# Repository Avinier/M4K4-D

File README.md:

# Makad / M4K4-D

> **Current project overview**: last reconciled **12 November 2026**
>
> Foundation approved: **14 August 2026** · V1 deadline: **5 December 2026**

**Makad**, technical designation **M4K4-D** and commonly shortened to **M4**, is a personal droid. M4 is intended to occupy the kind of companion role R2-D2 occupied for Luke Skywalker: recognizable, attentive, expressive, and full of character.

The central V1 priority is simple:

> **M4 should feel alive.**

Makad's defining advantage is expressiveness. That expression comes from what M4 understands, sees, and hears, and from how convincingly its display, status light, astromech audio, head, wheeled base, and timing communicate one intent.

## Authority

- [`project/00-foundation`](project/00-foundation/) is the product-intent authority.
- [`project/03-build`](project/03-build/README.md) governs every engineering decision, part selection, BOM change and CAD edit from 2026-09-28. Its ledger is [`decisions.md`](project/03-build/decisions.md) and its parts register is [`BOM.csv`](project/03-build/BOM.csv).
- [`project/01-system`](project/01-system/) and [`project/02-prototypes`](project/02-prototypes/) are read-only engineering reference. Where they disagree with `03-build`, `03-build` wins.

[`MEMORY.md`](MEMORY.md) is a short chronological log of the project's turning points.

## Current design

M4 is a battery-powered floor droid with a three-axis head, an animated face, a camera-side status light, body-mounted hearing and speech, and a two-wheel base. The head carries the display, camera, status light and C2 motion controller. The body carries the yaw stage, four I²S microphones, the speaker, main compute and the bought power modules; the chassis carries the battery, drive and floor sensors. Floor mode is primary; tabletop mode inhibits locomotion by default.

Drive geometry is Ø84 mm wheels on a ~170 mm track with a front ball caster and a mandatory rear anti-tip keel ([dimensional baseline](project/01-system/dimensional-baseline.md) v1.15). The whole robot is modelled in [`project/03-build/final/v1`](project/03-build/final/v1/README.md); subsystem CAD lives in [01-chassis](project/03-build/01-chassis/), [02-body](project/03-build/02-body/) and [03-head](project/03-build/03-head/).

### Selected components

States follow the [BOM](project/03-build/BOM.csv): selected parts are settled but not yet measured or bench-proven.

| Item | Selection | Record |
|---|---|---|
| Face display | Waveshare ESP32-S3-LCD-4.3, **no-touch, SKU 30493**: 800×480 IPS with on-board ESP32-S3/LVGL renderer | [display study](project/01-system/display-candidate-study.md) |
| Head camera | Raspberry Pi Camera Module 3 **Wide**, **SC0874**; ribbon crosses pitch and roll in a free loop behind the head | [D-105](project/03-build/decisions.md#d-105) |
| Main compute (C0) | **Raspberry Pi 5, 2 GB** with the official Active Cooler, on PCB-09 (2 × RS-422 link adapter) | [D-048](project/03-build/decisions.md#d-048), [04-pcbs](project/03-build/04-pcbs/README.md) |
| Head motion controller (C2) | Waveshare **ESP32-S3-Zero** on the custom PCB-12 carrier | [D-102](project/03-build/decisions.md#d-102) |
| Base controller (C3) | Espressif **ESP32-S3-DevKitC-1 v1.1** on the custom PCB-10 carrier | [04-pcbs](project/03-build/04-pcbs/README.md) |
| Head actuators | Yaw: **Waveshare ST3215-HS** at 11.1 V. Pitch and roll: **Feetech STS3045M** at 6.3 V. Candidates until bench tests B1–B6 | [D-046](project/03-build/decisions.md#d-046)–[D-049](project/03-build/decisions.md#d-049) |
| Drive | **ThinkRobotics MOT3001-6V230RPM** encoder gearmotors (received), two DRV8833 carriers, printed PETG/TPU wheels, Pololu #2691 ball caster | [D-003](project/03-build/decisions.md#d-003) |
| Battery | **2S1P Samsung INR18650-25R** (7.2 V, 18 Wh) with a bought TIFPS0629 protection board and copper ballast; charged off-board (ISDT PD60) | [D-093](project/03-build/decisions.md#d-093) |
| Power | Pololu #2813 pushbutton switch, two S18V20ALV servo rails, two S13V30F5 5 V rails, INA226 monitor | [D-094](project/03-build/decisions.md#d-094), [module selection](project/03-build/module-selection.md) |
| Audio and IMU | Visaton K 50 WP speaker, MAX98357A amp, 4 × INMP441 mics, Adafruit LSM6DSOX base IMU | [D-094](project/03-build/decisions.md#d-094) |
| Control split | C0 owns semantic behaviour; D1 renders eyes; C2 owns head trajectory and local safety; C3 owns base loops and local hazards. Links are differential UART; C2 relays face/light state locally | [control topology](project/01-system/control-topology-options.md) |

## Current build state

The design is ahead of the physical robot. The whole-robot CAD is integrated and checked; first parts have arrived; nothing is printed, wired or running.

| Area | State (2026-11-12) |
|---|---|
| CAD | Chassis, body and head v1 are integrated in `final/v1` with targeted checks. Tipping margin a_tip 1.670 neutral / 1.646 worst pose against 1.582 ([D-095](project/03-build/decisions.md#d-095)); camera-loop ballast keeps the worst-yaw margin above 1.5% ([D-105](project/03-build/decisions.md#d-105)). Not yet a fabrication release for body and head. |
| Electrical | D-093 replaced the custom power boards with bought modules. The [harness](project/03-build/05-harness/README.md) topology is drawn but on **electrical HOLD** ([D-096](project/03-build/decisions.md#d-096)). Custom boards: PCB-09 rev B routed; PCB-10/11/15 rev A; PCB-08/12/14/16 rev A drafts, not ordered. |
| Procurement | Modules and small parts ordered 2026-11-08; deliveries logged in [BOM-deliveries.md](project/03-build/BOM-deliveries.md). Open actions in [TODO.md](project/03-build/TODO.md). |
| Printing | Chassis print package exported to [04-print](project/04-print/README.md); body and head prints not started. |
| Software / firmware | [Firmware requirements](project/03-build/04-software/firmware-requirements.md) recorded; timebase, link contract and behaviour are specified more than implemented. |
| Physical tests | None run. Bench register N1–N12 and actuator tests B1–B6 are open. |

`visuals/` are provisional references; several show superseded details (mouths, ear microphones, yoke-mounted ears).

## Immediate next work

- **Receive and measure** the ordered parts; record them in the BOM and correct dependent CAD.
- **Run the bench tests**: power switch, servo and 5 V rails (N1–N12), Feetech actuators (B1–B6), pack protection acceptance.
- **Clear the harness HOLD** from measured peaks, then build and test the harness.
- **Finish the custom boards** (PCB-08, 12, 14, 16) and order all of them together.
- **Print and assemble the chassis**, then body and head, through [04-print](project/04-print/README.md).
- **Implement firmware and software** on the same timeline: C2/C3, C0 behaviour and perception, the serial link and face rendering.

## Documents

### Product intent: authoritative

- [Vision](project/00-foundation/vision.md)
- [V1 scope](project/00-foundation/v1-scope.md)
- [Constraints](project/00-foundation/constraints.md)
- [Success criteria](project/00-foundation/success-criteria.md)
- [Core interaction scenarios](project/00-foundation/core-interaction-scenarios.md)

### Build: governing

- [03-build overview](project/03-build/README.md): status, file map and build rules
- [Decisions ledger](project/03-build/decisions.md), [BOM](project/03-build/BOM.csv), [simplification plan](project/03-build/simplification-plan.md)
- [Whole robot (final v1)](project/03-build/final/v1/README.md) and its [print guide](project/03-build/final/v1/printguide.md)
- [Custom PCBs](project/03-build/04-pcbs/README.md), [harness](project/03-build/05-harness/README.md)
- [Printing](project/04-print/README.md)

### Engineering reference (read-only)

- [Dimensional and packaging baseline](project/01-system/dimensional-baseline.md)
- Ledgers: [mass/envelope](project/01-system/mass-envelope-ledger.md), [power/energy/thermal](project/01-system/power-energy-ledger.md), [candidate sourcing](project/01-system/candidate-sourcing-matrix.md)
- Studies: [control topology](project/01-system/control-topology-options.md), [display](project/01-system/display-candidate-study.md), [camera](project/01-system/camera-candidate-study.md), [head harness](project/01-system/head-harness-routing-study.md), [timebase](project/01-system/timebase.md)
- [System design brief](project/01-system/system-design-brief.md), [risk-prototype plan](project/01-system/risk-prototype-plan.md), [workbench](project/01-system/workbench.md), [run-record convention](project/01-system/run-record-convention.md)
- Risk prototypes: [head](project/02-prototypes/RP-01-head/), [electrical](project/02-prototypes/RP-02-electrical/README.md), [locomotion](project/02-prototypes/RP-03-locomotion/README.md), [coordination](project/02-prototypes/RP-04-coordination/README.md), [interaction](project/02-prototypes/RP-05-interaction/README.md), [CAD layouts](project/02-prototypes/RP-06-cad/README.md), [following](project/02-prototypes/RP-07-following/README.md)
- Earlier memory logs: [`archive/`](archive/)

## Repository

```
project/00-foundation/   product intent and constraints      authoritative
project/01-system/       system studies and ledgers          reference
project/02-prototypes/   risk prototypes and early CAD       reference
project/03-build/        decisions, BOM, CAD, PCBs, harness  governs
project/04-print/        print lab, workflow, STL exports
visuals/                 provisional renders
archive/                 earlier memory logs
MEMORY.md                chronological log of turning points
README.md                this orientation
```

## Identity and design direction

M4 is a droid, not a desktop assistant, smart speaker, or generic social robot. The approved direction is:

- strongly inspired by Star Wars droids;
- cyberpunk, rugged, scrappy, and characterful;
- mechanical rather than glossy or appliance-like;
- modular and screw-together, with visible fasteners, panels, seams, and service access as part of the personality;
- eyes only on the face, no mouth;
- approachable without optimizing for minimum size;
- open to substantial redesign from the current renders.

## V1 Core

V1 is not complete unless the following outcomes work together as one droid. Exact wording lives in [`v1-scope.md`](project/00-foundation/v1-scope.md) (SCOPE-01…21).

**Expression and character** — animated face on the onboard display; powered roll, pitch and yaw head motion; at least one controllable LED beside the camera; a builder-authored non-English astromech language; idle aliveness without manual control; display, LED, audio, head, base and timing express one intent; at least one bounded excited spin.

**Understanding and perception** — natural spoken interaction within the approved scenarios; invocation forms **"M4," "M4K4," and "Makad"**; visual acquisition of a nearby person or face; tracking maintained or reacquired through later-defined test cases.

**Mobility and following** — battery-powered wheeled floor droid; "come here" finds, approaches and stops at a bounded distance; "follow me" tracks the selected person through an approved indoor route; obstacles, stopping, target loss and unsafe conditions are handled without continuing blindly.

**Utility and entertainment** — display the time; create and signal timers and alarms; start Spotify playback through an approved integration; eyes "vibe" to music.

**Operation and construction** — untethered on onboard battery for at least 20 minutes; floor mode primary; tabletop mode inhibits locomotion by default and protects edges; accessible stop or cutoff with bounded failure; assembled, started, demonstrated, inspected and serviced from documentation.

**Candidate:** spatial/directional hearing, included only if it materially improves an approved interaction. Everything else is uncommitted; there is no permanent "never" list.

## Approved Core scenarios

Source: [`core-interaction-scenarios.md`](project/00-foundation/core-interaction-scenarios.md).

**1. Wake, socialize, assist.** M4 idles head-down. A person calls its name. M4 wakes as one coordinated performance: three-axis head rise, eyes, camera-side LED, astromech acknowledgement, face acquisition and gaze. A greeting produces an in-character response. The person can request the time, a timer, an alarm, or Spotify playback; M4 confirms visibly, performs it, and vibes during music.

**2. Come here and follow me.** On an approved floor, the person invokes M4 and says "come here." M4 acknowledges, searches, acquires, turns, approaches safely and stops approximately 0.6–0.9 m away. "Follow me" makes M4 follow through an approved route of up to about 3 m at no more than about 0.5 m/s while handling obstacles and target loss. When continuing is unsafe, M4 stops and says so. M4 performs an excited spin and settles.

## Success definition

V1 succeeds when M4 delivers these interactions as a convincing, repeatable droid encounter on battery power, not as a sequence of manually rescued subsystem demos. The validation categories and open thresholds are in [`success-criteria.md`](project/00-foundation/success-criteria.md) (SC-01…25).

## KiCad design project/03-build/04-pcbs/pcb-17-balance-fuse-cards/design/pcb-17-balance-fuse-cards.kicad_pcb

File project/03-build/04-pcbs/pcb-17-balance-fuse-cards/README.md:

# PCB-17 — Balance-tap fuse cards

Two small passive cards that put a 1 A very-fast fuse in each of the pack's three balance taps (B−, BM, B+) right at the PCB-01 BMS pads. These taps feed the rear balance port ahead of PCB-01 and the 15 A main fuse, so the cards are their only short-circuit protection ([D-111](../../decisions.md#d-111), [D-115](../../decisions.md#d-115), [D-116](../../decisions.md#d-116), [D-117](../../decisions.md#d-117)).

| | |
|---|---|
| Register | [04-pcbs board register](../README.md#board-register) |
| Project BOM | CH-103 in [BOM.csv](../../BOM.csv) |
| Location | Chassis tub, lying component side up on the PCB-01 (HW-391) BMS: card A at its +Y (BM/P) end, card B at its −Y (0V/8.4V) end, each under a 0.8 mm relief in the CH-106 plate |
| Final CAD | `BALANCE_FUSE` and `BMS_PADS` in [makad-v1.step.py](../../final/v1/cad/makad-v1.step.py); check `check_ch103_protection.py` |

## Stages

| Stage | Status | Revision / evidence | Date |
|---|---|---|---|
| 1. Design | **Rev A complete**; [fab/revA](fab/revA/README.md) written (do not order before the gates) | [design/](design/): Nightly ERC 0/0, netlist audit 13/13, parity DRC 0/0/0; [STEP](cad/pcb-17-balance-fuse-cards-revA.step) | 2026-11-18 |
| 2. Procure | Panelise with PCB-11 and PCB-15 (same 0.8 mm stackup) in the D-064 batch | — | — |
| 3. Integrate | Droid CAD envelopes match the KiCad outlines (card A 6 × 9, card B 9.5 × 10, 2.0 mm with fuse and potting); `check_ch103_protection` 12/12. Board STEP not yet swapped in by `pcb_integration.py` | Physical acceptance open | 2026-11-18 |

## Circuit

| Card | Fuse | Cell-side pad | Protected pad | Silk |
|---|---|---|---|---|
| A (6 × 9 mm) | F1, BM | J1 `BM_CELL` (from the HW-391 4.2V pad) | J2 `BM_FUSED` | `BM`; back `17A` |
| B (9.5 × 10 mm) | F2, B− | J3 `BMINUS_CELL` (0V pad) | J4 `BMINUS_FUSED` | `B-`; back `17B` |
| B | F3, B+ | J5 `BPLUS_CELL` (8.4V pad) | J6 `BPLUS_FUSED` | `B+` |

Fuses: Littelfuse 0466001.NRHF, 1206, 1 A, 63 VDC, 50 A interrupt, ~0.075 Ω cold. Each fuse's pin 1 faces its card's BMS pad end. Wire pads are 2.5 × 1.5 mm bare copper for AWG24 laid flat along X. Tracks are 0.8 mm, one straight column per tap. B− and B+ copper is 1.5 mm apart.

## Coordinates

KiCad (x, y down) to droid CAD: card A X = x − 59.0, Y = 124.0 − y; card B X = x − 70.7, Y = 86.0 − y. Board Z 0 is the card's underside on the BMS (droid Z 54.2). Fab origin (100, 110), the bottom-left of the two-card group.

## Open

- **Received HW-391:** confirm the pad corners (the `BMS_PADS` values are estimates from the listing photos) and the full board height. If board + card exceeds the pack-to-plate gap at either end, deepen that CH-106 relief, keeping at least a 1.5 mm roof, and re-run `check_ch103_protection.py`.
- **Potting:** thin silicone or epoxy, ≤ 0.6 mm over the fuse. The fuse ratings assume an uncoated part, so N5 is run with the cards potted ([D-116](../../decisions.md#d-116)).
- **N5:** the PD60 open-tap, adjacent-short and main-lead-off cases, plus 0.5 A fuse heating, per D-116. W02P stays unbuilt until N5 passes.

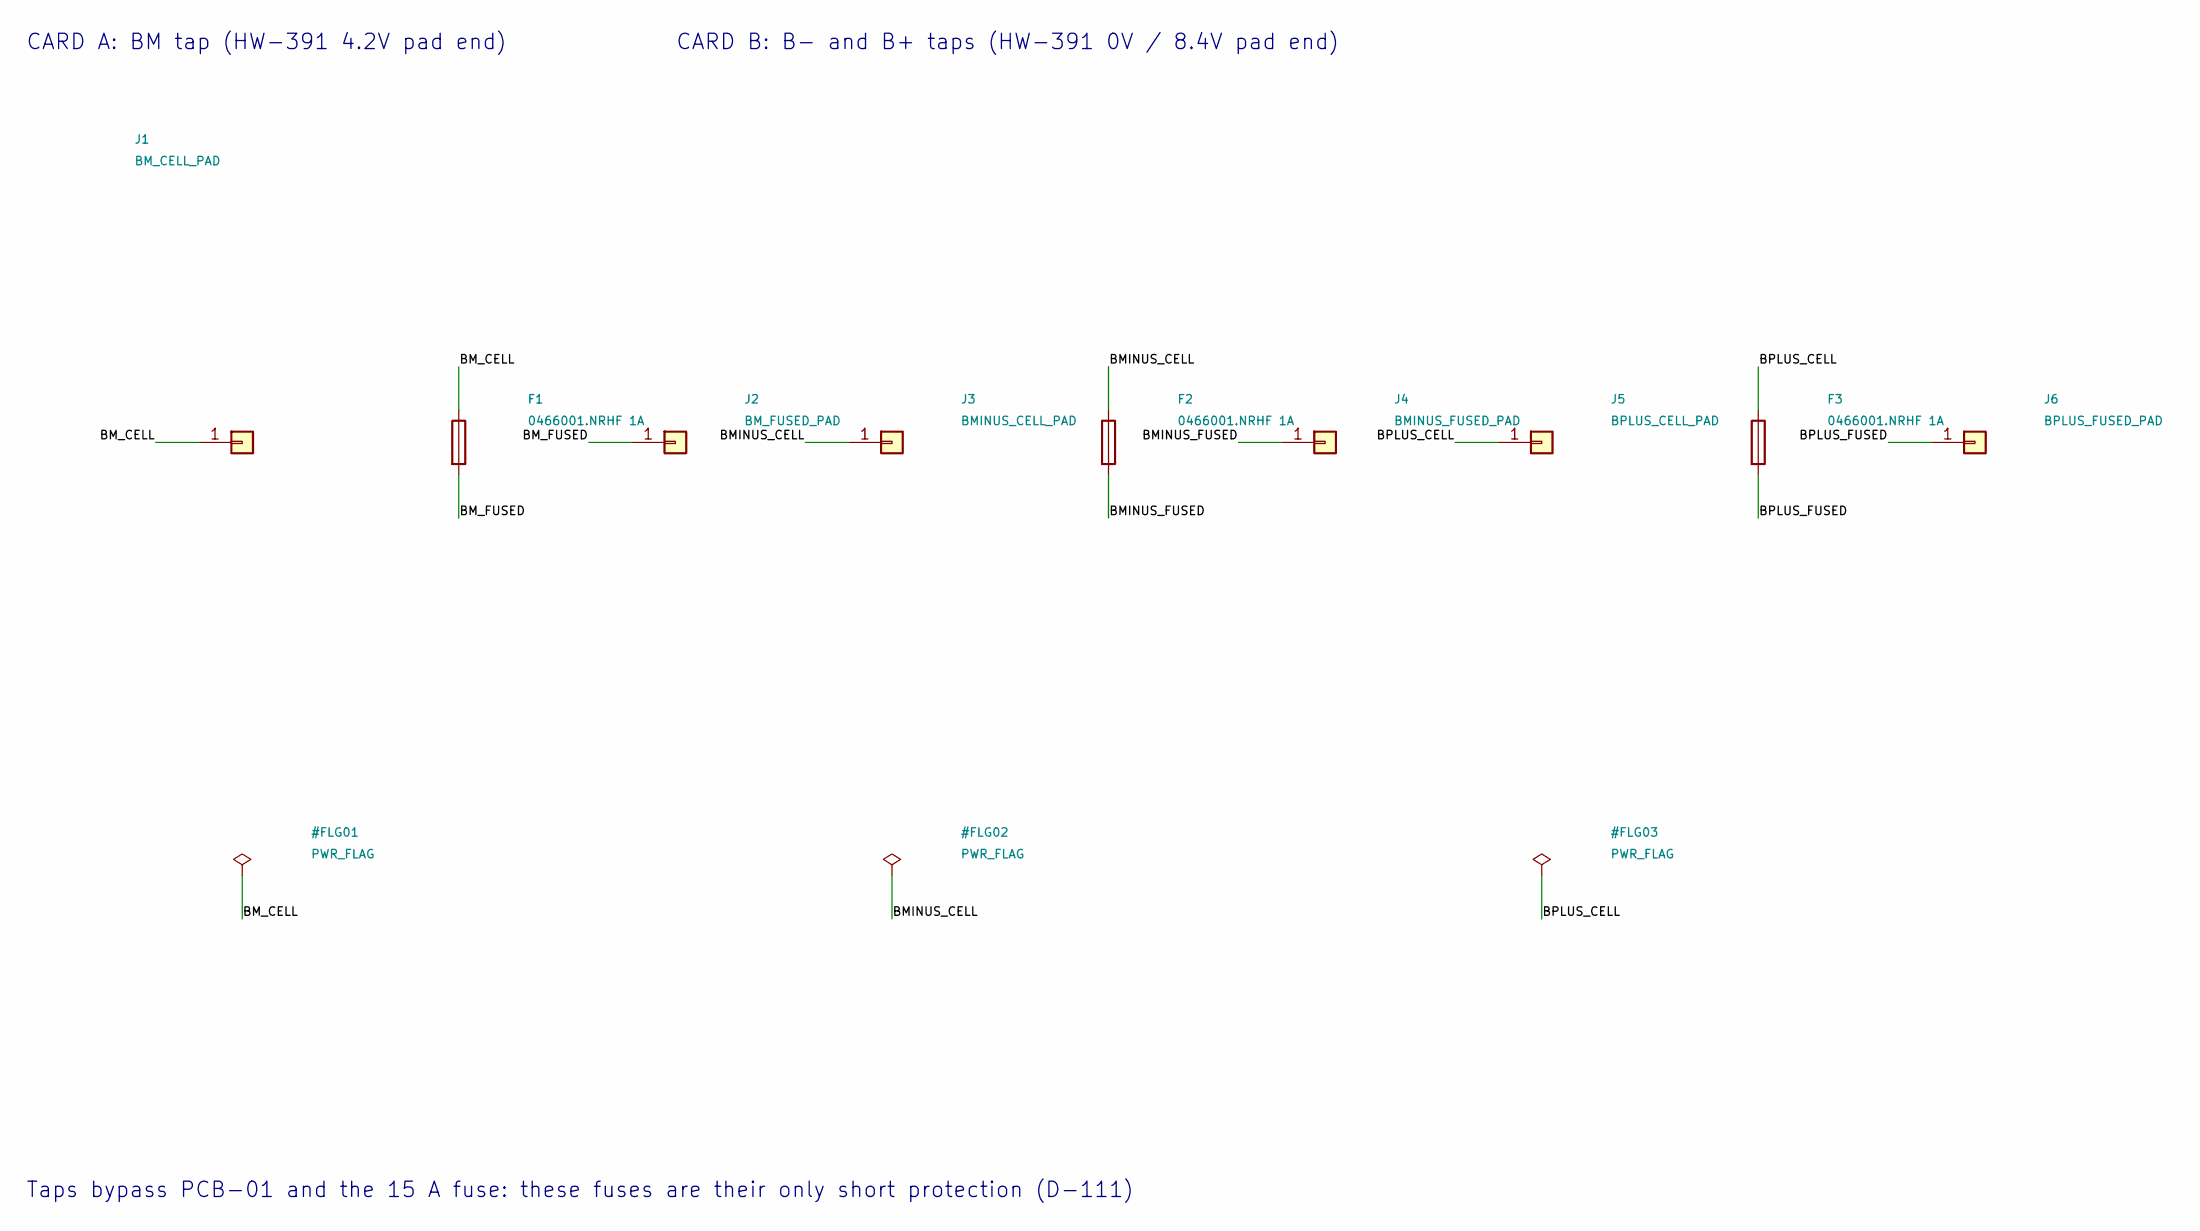
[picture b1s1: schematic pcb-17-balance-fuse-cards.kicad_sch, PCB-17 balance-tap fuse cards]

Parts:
F1, F2, F3: 0466001.NRHF 1A; Fuse_1206_3216Metric
J1: BM_CELL_PAD; WirePad_1x01_2.5x1.5mm
J2: BM_FUSED_PAD; WirePad_1x01_2.5x1.5mm
J3: BMINUS_CELL_PAD; WirePad_1x01_2.5x1.5mm
J4: BMINUS_FUSED_PAD; WirePad_1x01_2.5x1.5mm
J5: BPLUS_CELL_PAD; WirePad_1x01_2.5x1.5mm
J6: BPLUS_FUSED_PAD; WirePad_1x01_2.5x1.5mm

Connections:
/BMINUS_CELL: F2.1, J3.1 (Pin_1_1)
/BMINUS_FUSED: F2.2, J4.1 (Pin_1_1)
/BM_CELL: F1.1, J1.1 (Pin_1_1)
/BM_FUSED: F1.2, J2.1 (Pin_1_1)
/BPLUS_CELL: F3.1, J5.1 (Pin_1_1)
/BPLUS_FUSED: F3.2, J6.1 (Pin_1_1)

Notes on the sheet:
CARD A: BM tap (HW-391 4.2V pad end)
CARD B: B- and B+ taps (HW-391 0V / 8.4V pad end)
Taps bypass PCB-01 and the 15 A fuse: these fuses are their only short protection (D-111)

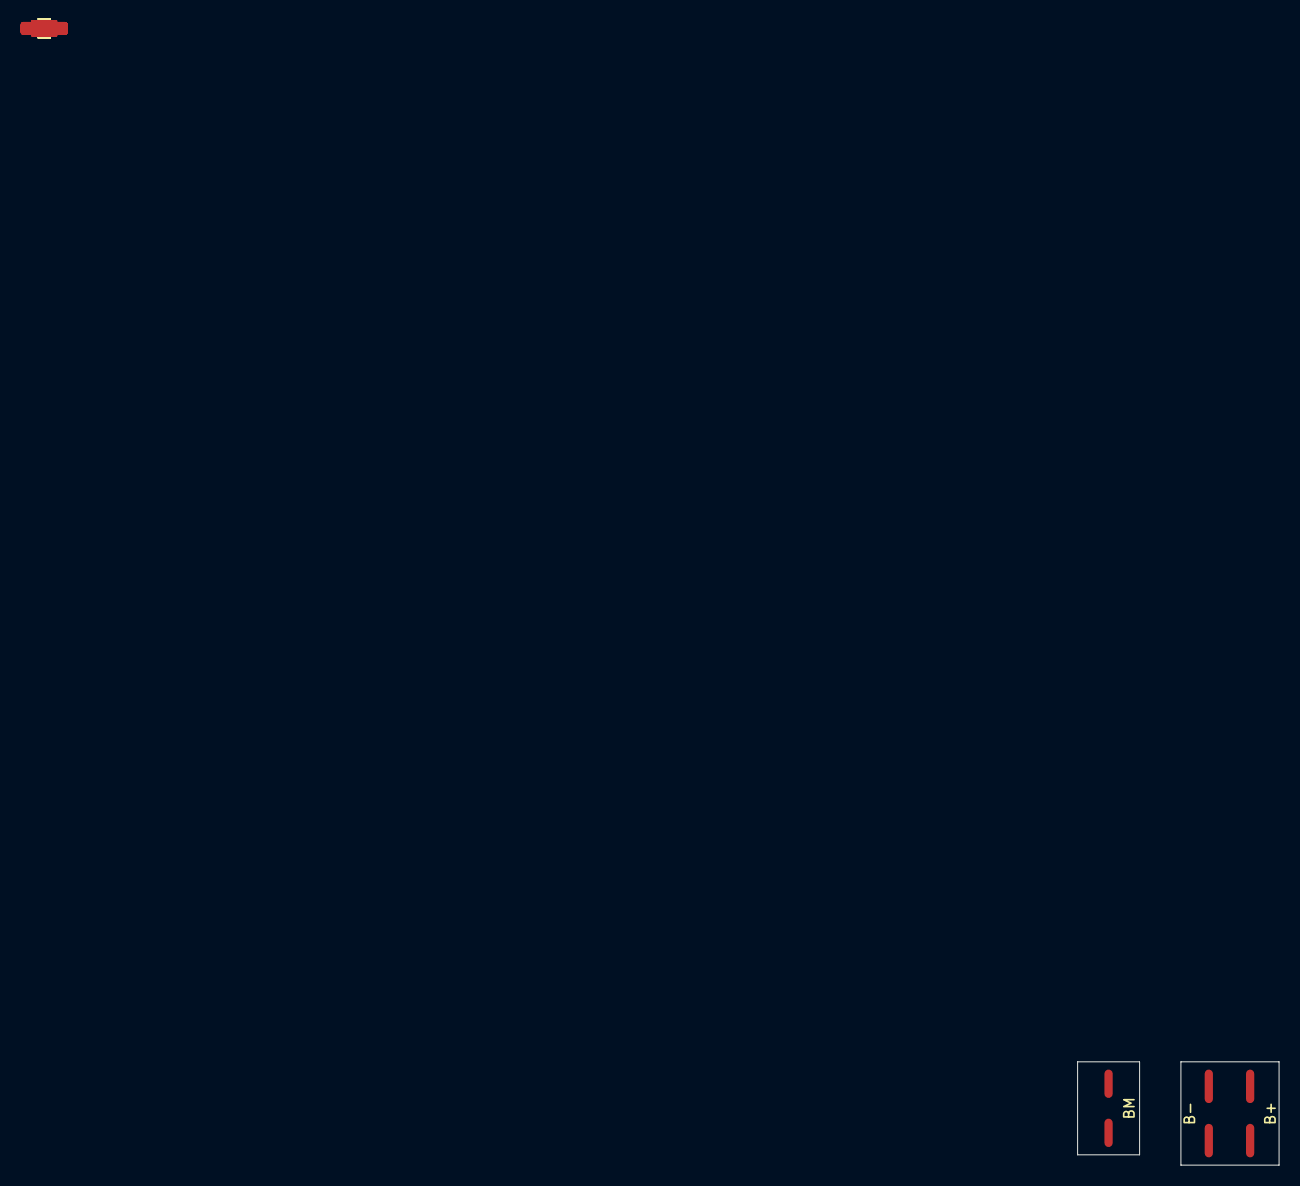
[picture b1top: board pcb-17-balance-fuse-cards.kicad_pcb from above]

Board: 2 copper layers, 9 parts (0 on the bottom side), 6 nets.

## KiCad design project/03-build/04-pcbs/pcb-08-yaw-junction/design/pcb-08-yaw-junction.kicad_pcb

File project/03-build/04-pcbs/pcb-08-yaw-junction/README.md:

# PCB-08 — Yaw junction, rev B (D-107)

The stationary body junction for W47: three power pairs pass from J8-1 to J8-9; the C0 head link and servo bus leave on J8-10. The B0091 camera link bypasses this board. Rev A and its FFC fab package are historical and must not be ordered.

| Stage | State / evidence |
|---|---|
| Design | Rev B electrical draft: [design](design/), Nightly ERC 0 errors/0 warnings; exported pin audit 12/12 and W47/PCB-12 audit 5/5; DRC 0 errors, 0 unconnected, 0 parity differences, six explained library-copy warnings |
| Procure | **HOLD — do not order.** D-064 batch, received-cable checks, populated bench gates and fab DFM remain open |
| Integrate | Rev B STEP selected by final/v1/cad/pcb_integration.py. Body/plug/mount checks: `check_d107_body.py`; whole-robot check: `check_pcb_integration.py`. First real board and mount fit remain open |

## Frozen interfaces

KiCad reference designators differ from harness names. Use marked contact numbers, never visual left-to-right guesses.

| KiCad | Harness | Part / pin order |
|---|---|---|
| J1 | J8-1 input | Molex 43045-0621 Micro-Fit 3.0 2×3 RA: 1 +6V3_HEAD_PR, 2 +5V_C2, 3 +5V_DISPLAY, 4 GND_HEAD, 5 GND_C2, 6 GND_DISPLAY |
| J3 | J8-9 W47 power | Same header and **same numbered map as J1**; mouth +X, opposed to J1's −X mouth |
| J2 | J8-4 W24 | JST BM06B-GHS-TBT GH6: 1 LINK_GND, 2 C0TX+, 3 C0TX−, 4 C2TX−, 5 C2TX+, 6 isolated |
| J4 | J8-10 W47 signals | GH6: 1 GND_SIG, 2 C0TX+, 3 C0TX−, 4 C2TX−, 5 C2TX+, 6 SERVO_DATA |
| J5 | J8-8 yaw | Molex 22-03-5035 / 5267-03A: 1 GND_SIG, 2 +11V1_YAW, 3 SERVO_DATA; match received Feetech lead |
| J6 | W17 solder pads | 1 +11V1_YAW, 2 GND_SIG; strain relieve before pads |
| R1 | ground option | 0Ω 0805 from LINK_GND to GND_SIG; ferrite/resistor fallback needs bench evidence |

The three power returns stay separate on PCB-08. GND_SIG includes the yaw return, so the accepted W24/yaw loop and its ground-current/common-mode checks from D-100 remain. PCB-12 joins its local grounds through R1/R7/R10; W47 J8-9.4 and J8-10.6 branch to PCB-12 J2 in the head. Only three conductors cross the roll joint.

## Envelope and routing amendment

The six real connector courtyards do not fit the proposed 32×21 mm core. Rev B is **34×25×1.6 mm**, world X−22…12, Y−46…−21, Z112…113.6. The old FFC extension to X20 is removed. All parts are on the top. Placement is read back from the saved board, and the populated STEP is checked against the Pi's real face bounds and the complete edited body.

Rev B uses **four layers with at least35µm FINISHED copper on every layer**. Dedicated solid +6V3_HEAD_PR and GND_HEAD fills on In1/In2 carry the head rail with solid pad connections, around the1.0mm seed tracks. Other power returns remain separate; there is no shared ground plane. C2/display branches remain0.5mm; yaw supply and return are1.5mm outer tracks; signals0.2mm. The nominal stack is0.035/0.20/0.035/1.06/0.035/0.20/0.035mm. Obtain written fab confirmation of finished inner copper:17.5µm is not an accepted substitution.

[Power copper audit](design/power-copper-audit.json) measures the actual filled copper and solves a0.1mm resistor sheet with equipotential PTH disks. At35µm/60°C it predicts about11.33mV total drop and0.0272W loss for the2.4A head rail, excluding barrels, contacts and solder. Half-thickness inner copper doubles both. This is an electrical screen, not thermal qualification; N2(b) must measure terminal voltage and PCB temperature in the closed body.

PCB-08 seats in a droid-owned edge cradle, with a removable front keeper and one M2×4 screw. It does not gain unreviewed mounting holes. The corrected cradle has a broad9.6×18mm web, deep beams and second upper tie into the frame. The first actual solid-root PETG print must pass100N connector-direction proof without cracking or permanent set; the hand screen is not a strength certification. Remove plugs and keeper before board removal; the CAD assembly check owns the removal path.

The six DRC warnings are `lib_footprint_mismatch` on J2/J4/J5/R1/TP1/TP2: their board copies deliberately put silk/reference graphics on Fab (and use the recorded model copies). The [pad audit](design/footprint-pad-audit.json) confirms all nine footprint land patterns match their libraries. No clearance or connection violation is waived. J6 is bare copper; KiCad's named wire model is absent and is not required to represent a populated component.

## Reproduce

Use the project Python for generators and KiCad **10.99 Nightly** for all electrical outputs. The documented headless kfile workflow is used; no autorouter.

```sh
rtk proxy .venv/bin/python project/03-build/04-pcbs/pcb-08-yaw-junction/design/build_schematic.py
rtk proxy .venv/bin/python project/03-build/04-pcbs/pcb-08-yaw-junction/design/layout_pcb08.py
rtk proxy .venv/bin/python project/03-build/04-pcbs/pcb-08-yaw-junction/design/export_revB.py
rtk proxy .venv/bin/python project/03-build/04-pcbs/pcb-08-yaw-junction/design/audit_netlist.py
rtk proxy .venv/bin/python project/03-build/04-pcbs/pcb-08-yaw-junction/design/audit_w47.py
```

ERC is run separately with `kicad-cli sch erc --severity-all`. The export script refuses electrical errors, then exports the netlist, schematic PDF, STEP, Gerbers, drill, BOM and placements. All fab coordinates use the same bottom-left origin, world(−22,−46). Review [fab/revB](fab/revB/README.md); [fab/revA](fab/revA/README.md) remains the superseded record.

## Before ordering / physical acceptance

- Verify genuine connector contacts for **AWG22 and AWG26** in the Micro-Fit plug; a contact for 20–24AWG must not be assumed suitable for AWG26. Buy compatible pre-crimped GH leads.
- Confirm J5/servo cavity order and conductor ratings against received parts. Trim conductive THT tails to ≤1.5 mm below the board and recheck clearance.
- Confirm first printed cradle, keeper and body strain relief; connector mating and head removal with the received housings, through the Ø18 liner.
- N2(b): terminal voltage under the 2.4A head allowance and low pack; review M2's 6.3V setpoint after removing the ribbon loss. Retain minimum terminal target5.23V.
- Measure W24 ground current at yaw stall, common-mode voltage with simultaneous display/servo load, and bus edges at J8-8.
- Complete fab DFM/stack-up acceptance and the six-board D-064 batch release. PCB-12 still has K2 LED-driver and received Zero/B5 gates. K3 D1 power inlet remains open.
- Camera C0–C4 and first-hour wear checks are in [the D-107 plan](../../head-umbilical-plan.md); they cannot be closed by CAD.

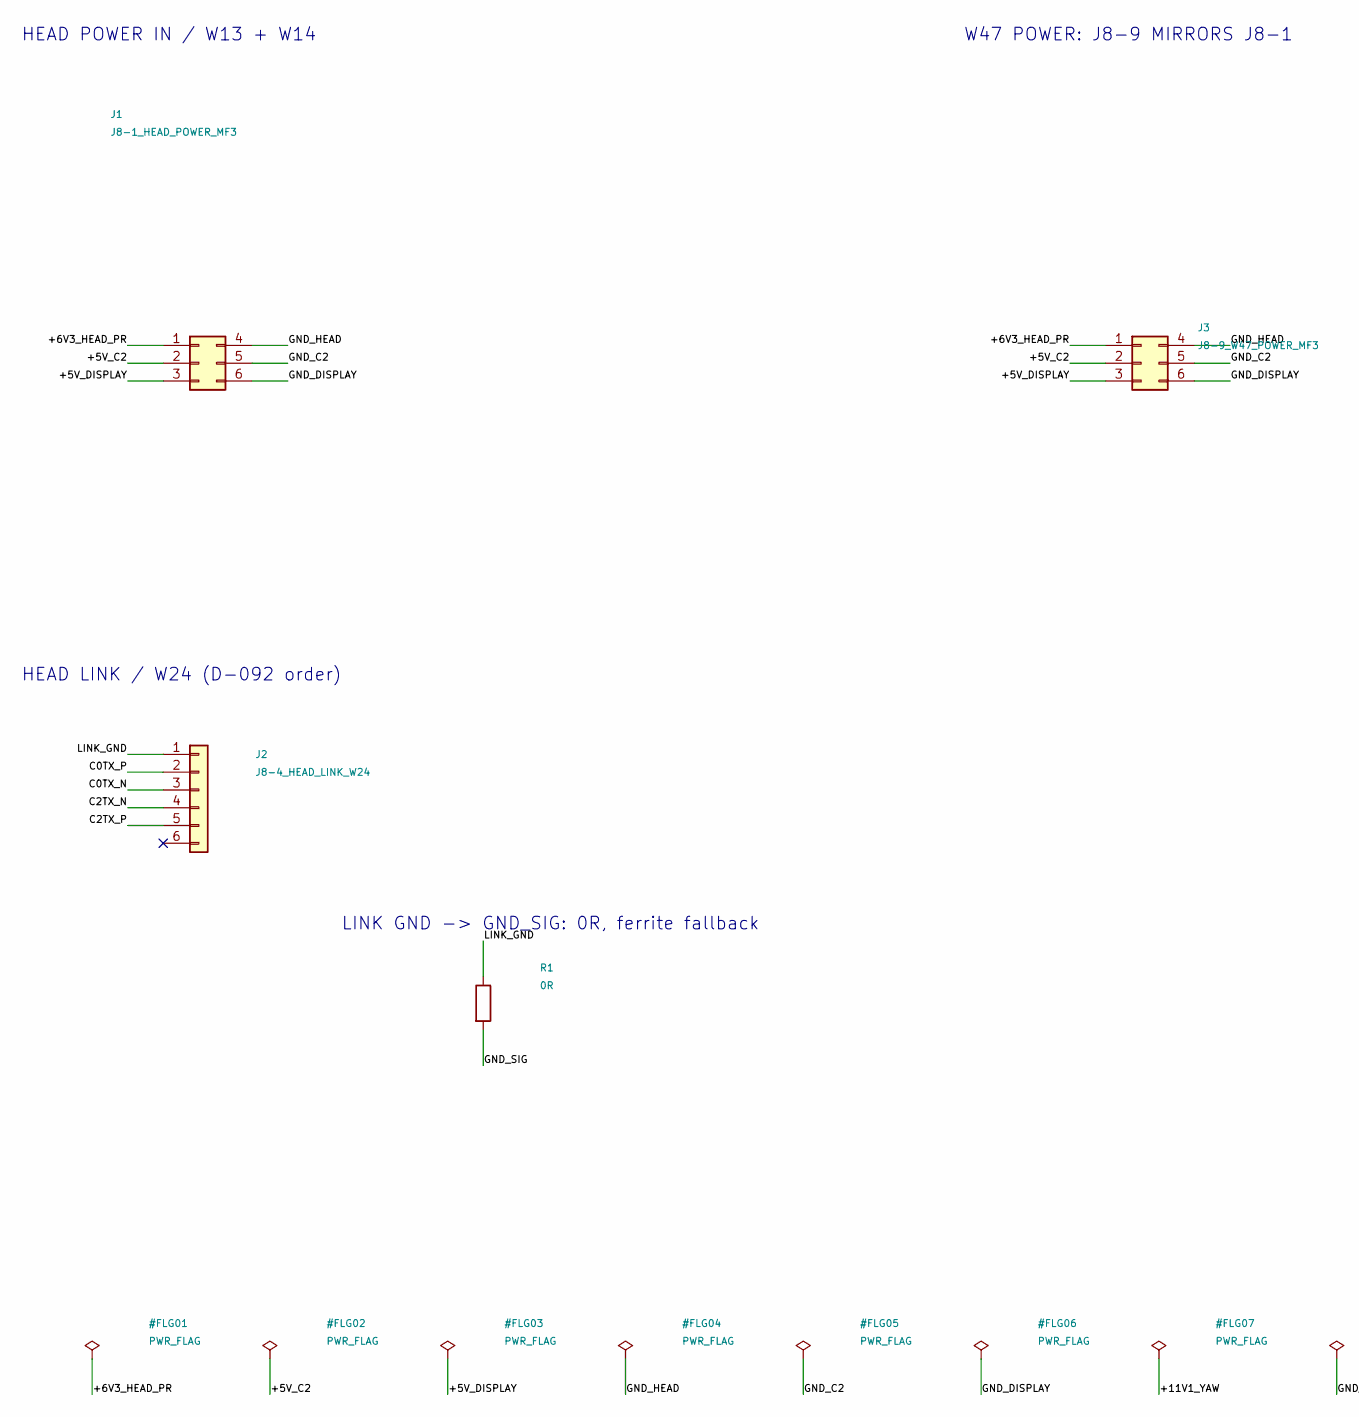
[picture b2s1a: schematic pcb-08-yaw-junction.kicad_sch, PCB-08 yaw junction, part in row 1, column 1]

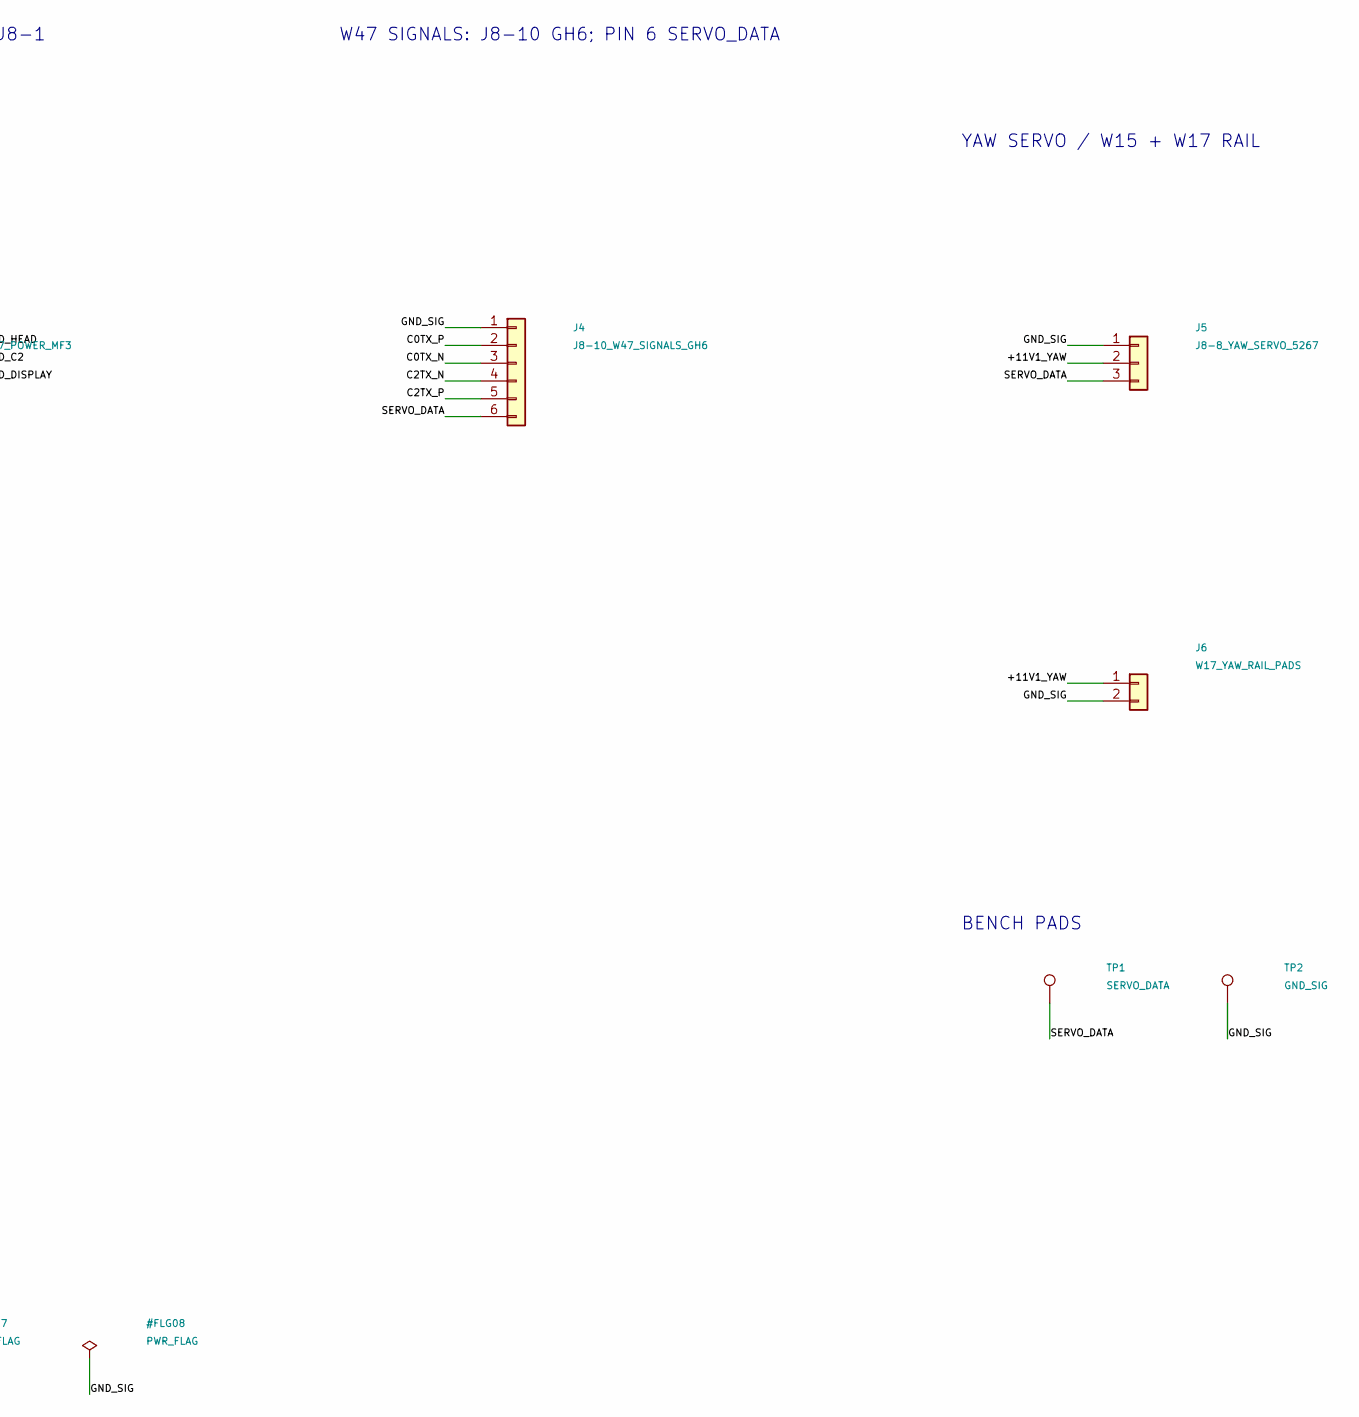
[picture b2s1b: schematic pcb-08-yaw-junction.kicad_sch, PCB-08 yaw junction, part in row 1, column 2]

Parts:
J1: J8-1_HEAD_POWER_MF3; Molex_Micro-Fit_3.0_43045-0621_2x03-1MP_P3.00mm_Horizontal
J2: J8-4_HEAD_LINK_W24; JST_GH_BM06B-GHS-TBT_1x06-1MP_P1.25mm_Vertical
J3: J8-9_W47_POWER_MF3; Molex_Micro-Fit_3.0_43045-0621_2x03-1MP_P3.00mm_Horizontal
J4: J8-10_W47_SIGNALS_GH6; JST_GH_BM06B-GHS-TBT_1x06-1MP_P1.25mm_Vertical
J5: J8-8_YAW_SERVO_5267; Molex_SPOX_5267-03A_1x03_P2.50mm_Vertical
J6: W17_YAW_RAIL_PADS; SolderWire-0.5sqmm_1x02_P4.6mm_D0.9mm_OD2.1mm
R1: 0R; R_0805_2012Metric
TP1: SERVO_DATA; TestPoint_Pad_D1.0mm
TP2: GND_SIG; TestPoint_Pad_D1.0mm

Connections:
/+5V_C2: J1.2, J3.2
/+5V_DISPLAY: J1.3, J3.3
/+6V3_HEAD_PR: J1.1, J3.1
/+11V1_YAW: J5.2, J6.1
/C0TX_N: J2.3, J4.3
/C0TX_P: J2.2, J4.2
/C2TX_N: J2.4, J4.4
/C2TX_P: J2.5, J4.5
/GND_C2: J1.5, J3.5
/GND_DISPLAY: J1.6, J3.6
/GND_HEAD: J1.4, J3.4
/GND_SIG: J4.1, J5.1, J6.2, R1.2, TP2.1 (1_1)
/LINK_GND: J2.1, R1.1
/SERVO_DATA: J4.6, J5.3, TP1.1 (1_1)

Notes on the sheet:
HEAD POWER IN / W13 + W14
HEAD LINK / W24 (D-092 order)
LINK GND -> GND_SIG: 0R, ferrite fallback
W47 POWER: J8-9 MIRRORS J8-1
W47 SIGNALS: J8-10 GH6; PIN 6 SERVO_DATA
YAW SERVO / W15 + W17 RAIL
BENCH PADS

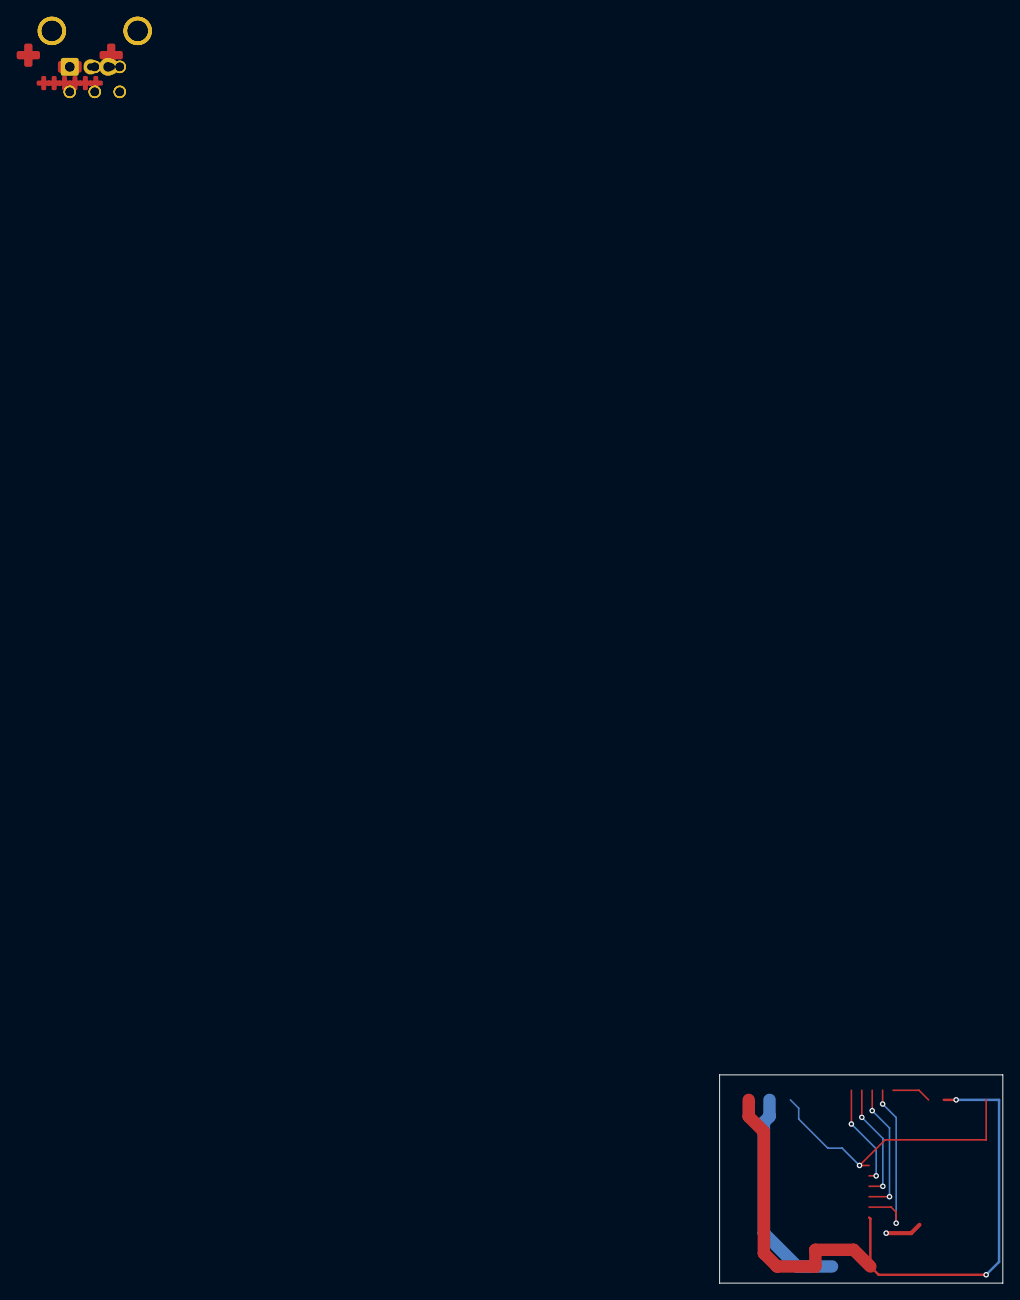
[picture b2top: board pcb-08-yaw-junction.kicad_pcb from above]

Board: 4 copper layers, 34.0 x 25.0 mm, 9 parts (0 on the bottom side), 14 nets.

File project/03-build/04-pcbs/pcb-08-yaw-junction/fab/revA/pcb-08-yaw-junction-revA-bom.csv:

"Comment","Designator","Footprint","Quantity","MPN","Manufacturer","LCSC Part #"
"J8-1_HEAD_POWER_MF3","J1","pcb08:Molex_Micro-Fit_3.0_43045-0621_2x03-1MP_P3.00mm_Horizontal","1","43045-0621","Molex",""
"J8-4_HEAD_LINK_W24","J2","Connector_JST:JST_GH_BM06B-GHS-TBT_1x06-1MP_P1.25mm_Vertical","1","BM06B-GHS-TBT(LF)(SN)(N)","JST",""
"J8-6_W42_POWER_FFC","J3","fh34:Hirose_FH34SRJ-22S-0.5SH_1x22_P0.50mm","1","FH34SRJ-22S-0.5SH(99)","Hirose",""
"J8-7_W43_SIGNAL_FFC","J4","fh34:Hirose_FH34SRJ-22S-0.5SH_1x22_P0.50mm","1","FH34SRJ-22S-0.5SH(99)","Hirose",""
"J8-8_YAW_SERVO_5267","J5","Connector_Molex:Molex_SPOX_5267-03A_1x03_P2.50mm_Vertical","1","22-03-5035 (5267-03A)","Molex",""
"0R","R1","Resistor_SMD:R_0805_2012Metric","1","RC0805JR-070RL","Yageo",""
